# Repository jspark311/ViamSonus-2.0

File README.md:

# Viam Sonus 2.0

An audio router board with integrated volume control and buffered output.

### FEATURES:
  * 12 input channels that are arbitrarily routable to any of 8 output channels.
* Onboard digital potentiometers on the input side with non-volatile storage. Pots are logarithmic with zero-cross detection, and are paired in order with their input numbers on the board's silkscreen.
* Onboard op-amps on the output side with 300mA drive capability to provide buffering for direct-drive of line-level signals.
* Onboard buffered voltage divider with exposed output and 300mA drive capability to aid design and implementation of input buffers.
* Resistors added to the input-side of the switch, but after the potentiometers to allow for simple resistance mixing of signals simply by routing two inputs to a given output without risking damage. Some caveats apply (discussed below).
* Input-side is left free-form to allow use with single-ended (unbalanced) or differential (balanced) signals, and/or DC-biased sources.
* Safe for 5v audio signals.
* Isolated analog and digital power planes.
* Silkscreen reflects the envisioned usage (stereo signals), but the driver allows for easy grouping of any number of channels.
* Breadboard-friendly

#### [Hackaday.io Page](https://hackaday.io/project/168501-viam-sonus-20)

#### [Order from Tindie](https://www.tindie.com/products/18586/)

------------------------

### What is in this repository:

**./doc**:  Location for documentation

**./KiCAD**:  Hardware design files

**./Arduino**:  Arduino driver

**./linux**:  Linux wrappers and utility program

------------------------

### Encountering real world audio signals

#### Mixing, ducking, and cross-fade

To avoid damaging the board, input-side circuits should be designed to limit
peak channel currents if mixing is going to be used. Discourse on that topic can
be found in [a separate document](https://joshianlindsay.com/index.php?id=184).

#### Tips on channel layout

The driver sees the board as 12 mono inputs with discrete volume control routed
to 8 mono outputs. The driver presents a channel-grouping layer to the user application
that largely abstracts the underlying mono channels. But since the DS1881 was
intended as a stereo device, it has properties that support that use...

  * Resistances are matched on its two halves.
  * Both halves can be set with a single bus operation (and thus happen concurrently)

So if you intend on using Viam Sonus to handle stereo inputs, you _can_ use whatever
two channels for left and right that you like, and the driver will make it work. But it
will cost an extra bus operation to set the volume for the pair, and the channel
resistance match might be as loose as +/-20%. So if you can, you will get better
results by keeping stereo pairs on matched channels.

The output channels are also paired into the output buffers, but the choice of
keeping those matched (or not) will have less-tangible consequences.

------------------------

### Notes on driver features:

#### Channel grouping

By default, there are no channel groups, and the API operates on the level of
discrete mono channels. But many application will want to manage _groups of channels_.

Channel groups come in two flavors: Input and Output. Each type has a unique API.

#### Preserve-on-destroy

When the driver instance for the switch is destroyed, the default behavior is to
put the hardware into a known state (reset). This opens all routes. Use-cases
that want the hardware state to outlive the driver's life cycle are possible by
setting preserveOnDestroy(true) ahead of `init()`, like so...

    // Class initializes with the existing state of the hardware.
    vs.preserveOnDestroy(true);
    vs.init(&Wire);

Since `init()` will also call `reset()` by default, preserveOnDestroy must be
enabled prior to `init()` to achieve the desired result (both sides of the driver life cycle).

#### Preserving and restoring hardware states

The driver provides a means of cloning prior states to and from a buffer.
Possible reasons for doing this might be...

  * Higher bus efficiency during `init()`.
  * Major code savings, since you can skip configuring the hardware and the class with discrete function calls.
  * Storage of complete board configurations that can be fully re-established with a minimum of overhead.

Saving the current state can be done like this (from the example sketch)...

    uint8_t buffer[VIAMSONUS_SERIALIZE_SIZE];
    unsigned int written = vs.serialize(buffer, VIAMSONUS_SERIALIZE_SIZE);
    if (VIAMSONUS_SERIALIZE_SIZE == written) {
      // Everything worked. Do what you will with the buffer.
    }

Restoring the state from a buffer can be done either upon construction...

    uint8_t buf[VIAMSONUS_SERIALIZE_SIZE] = {
      0x01, 0x00, 0x00, 0x00, 0x00, 0x01, 0x70, 0x0A, 0x00, 0x00, 0x00, 0x00,
      0x00, 0x00, 0x00, 0x00, 0x00, 0x00, 0x00, 0x00, 0x00, 0x00, 0x01, 0x28,
      0x00, 0x3F, 0x3F, 0x06, 0x01, 0x28, 0x00, 0x3F, 0x3F, 0x06, 0x01, 0x29,
      0x00, 0x3F, 0x3F, 0x06, 0x01, 0x29, 0x00, 0x3F, 0x3F, 0x06, 0x01, 0x2A,
      0x00, 0x3F, 0x3F, 0x06, 0x01, 0x2A, 0x00, 0x3F, 0x3F, 0x06 ...
    };
    ViamSonus vs(buf, VIAMSONUS_SERIALIZE_SIZE);

...or after a successful `init()`...

    // Literally anywhere in the sketch...
    vs.unserialize(buf, VIAMSONUS_SERIALIZE_SIZE);

If done by construction, the configuration will be written to the class immediately,
and to the hardware during `init()`.

Invocation of `unserialize()` will immediately result in I/O as the new
configuration is imparted, but the fields (if any) that are otherwise required for
construction will be ignored.

------------------------

### Usage under Arduino

In order to use this driver, you also need the Arduino drivers for the elements on the board. Clone the following repos into your user libraries (wherever you keep them):

[DS1881 Driver](https://github.com/jspark311/DS1881-Breakout/tree/master/Arduino)

[ADG2128 Driver](https://github.com/jspark311/ADG2128-Breakout/tree/master/Arduino)

[StringBuilder and DataStructures](https://github.com/jspark311/CppPotpourri)

After you've done that, you ought to be able to include the ViamSonus driver.

------------------------

### Usage under Linux

Fortunately, the Viam Sonus router board doesn't have any interrupt pins, which makes running it in userland fairly easy with existing kernel drivers for i2c and GPIO. The reset pin isn't _strictly_ required. It can be tied high.

Just like the Arduino driver, you will need additional libraries. If you've already done
the setup for exposing the GPIO pin and i2c character device in your kernel config, you
ought to be able to do these things...

    git clone https://github.com/jspark311/ViamSonus-2.0.git
    cd ViamSonus-2.0/linux
    ./downloadDeps.sh
    make DEFAULT_I2C_DEV=/dev/i2c-1 DEFAULT_RESET_PIN=/sys/class/gpio/gpio18
    sudo make install

------------------------

Front | Back
:-------:|:------:
  |

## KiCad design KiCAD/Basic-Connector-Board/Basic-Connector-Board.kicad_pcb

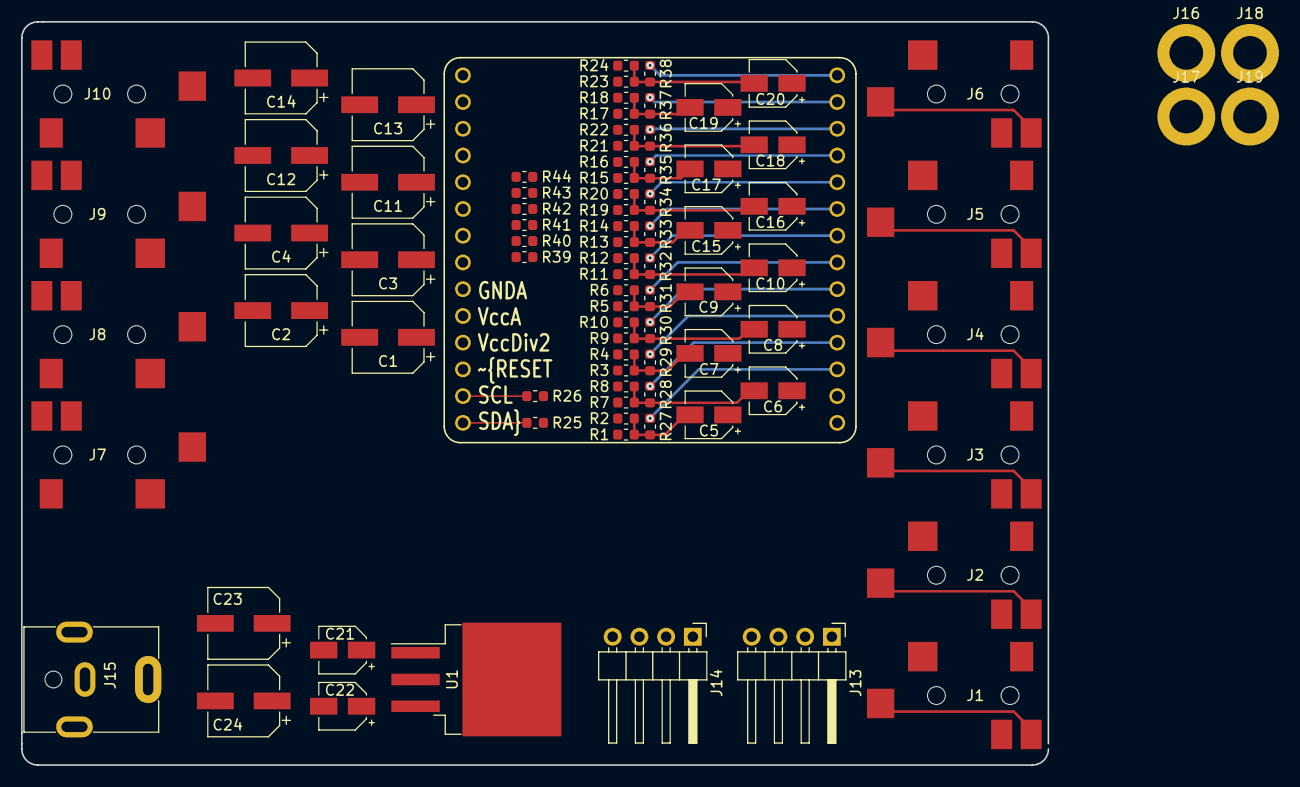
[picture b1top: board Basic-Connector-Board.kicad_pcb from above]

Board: 4 copper layers, 97.5 x 70.6 mm, 88 parts (1 on the bottom side), 67 nets.

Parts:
C1, C2, C3, C4, C11, C12, C13, C14, C23, C24: 100uF; CP_Elec_6.3x5.4_Nichicon
C5, C6, C7, C8, C9, C10, C15, C16, C17, C18, C19, C20: 3.3uF; CP_Elec_4x5.4
C21, C22: 10uF; CP_Elec_4x5.4
J1, J2, J3, J4, J5, J6, J7, J8, J9, J10: AudioJack3_Ground_Switch; SJ2-3593D-SMT-TR
J11, J12: Conn_01x14_Male; PinHeader_1x14_P2.54mm_Vertical
J13, J14: Conn_01x04; PinHeader_1x04_P2.54mm_Horizontal
J15: 6.5 - 20v; PJ-063AH
J16, J17, J18, J19: Conn_01x01; MountingHole_3.2mm_M3_ISO14580_Pad
R1, R2, R3, R4, R5, R6, R7, R8, R9, R10, R11, R12, R13, R14, R15, R16, R17, R18, R19, R20, R21, R22, R23, R24, R39, R40, R41, R42, R43, R44: 20k; R_0603_1608Metric
R25, R26, R27, R28, R29, R30, R31, R32, R33, R34, R35, R36, R37, R38: 2k; R_0603_1608Metric
U1: LM1085; TO-263-3_TabPin2

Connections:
/ANAGND: C21.2, C22.2, C23.2, C24.2, J1.S, J2.S, J3.S, J4.S, J5.S, J6.S, J7.S, J8.S, J9.S, J10.S, J12.6, J13.1, J15.2, R2.1, R4.1, R6.1, R8.1, R10.1, R12.1, R14.1, R16.1, R18.1, R20.1, R22.1, R24.1, U1.2
/ANAVcc: C22.1, C24.1, J12.5, J13.4, R1.1, R3.1, R5.1, R7.1, R9.1, R11.1, R13.1, R15.1, R17.1, R19.1, R21.1, R23.1, U1.3
/Biased-In-L-0: J11.3, R27.2
/Biased-In-L-1: J11.5, R29.2
/Biased-In-L-2: J11.7, R31.2
/Biased-In-L-3: J11.9, R33.2
/Biased-In-L-4: J11.11, R35.2
/Biased-In-L-5: J11.13, R37.2
/Biased-In-R-0: J11.4, R28.2
/Biased-In-R-1: J11.6, R30.2
/Biased-In-R-2: J11.8, R32.2
/Biased-In-R-3: J11.10, R34.2
/Biased-In-R-4: J11.12, R36.2
/Biased-In-R-5: J11.14, R38.2
/GND: J11.2, J13.2, J16.1, J17.1, J18.1, J19.1
/Out-L-0: C1.1, J12.7
/Out-L-1: C3.1, J12.9
/Out-L-2: C11.1, J12.11
/Out-L-3: C13.1, J12.13
/Out-R-0: C2.1, J12.8
/Out-R-1: C4.1, J12.10
/Out-R-2: C12.1, J12.12
/Out-R-3: C14.1, J12.14
/SCL: J12.2, J14.2, R26.2
/SDA: J12.1, J14.3, R25.2
/VIn+: C21.1, C23.1, J15.1, U1.1
/Vcc: J11.1, J13.3, R25.1, R26.1
/VccDiv2: J12.4, J14.4, R39.2, R40.2, R41.2, R42.2, R43.2, R44.2
/~RESET: J12.3, J14.1
unnamed: C1.2, J7.T
unnamed: C2.2, J7.R
unnamed: C3.2, J8.T
unnamed: C4.2, J8.R
unnamed: C5.1, J1.T
unnamed: C5.2, R1.2, R2.2, R27.1
unnamed: C6.1, J1.R
unnamed: C6.2, R7.2, R8.2, R28.1
unnamed: C7.1, J2.T
unnamed: C7.2, R3.2, R4.2, R29.1
unnamed: C8.1, J2.R
unnamed: C8.2, R9.2, R10.2, R30.1
unnamed: C9.1, J3.T
unnamed: C9.2, R5.2, R6.2, R31.1
unnamed: C10.1, J3.R
unnamed: C10.2, R11.2, R12.2, R32.1
unnamed: C11.2, J9.T
unnamed: C12.2, J9.R
unnamed: C13.2, J10.T
unnamed: C14.2, J10.R
unnamed: C15.1, J4.T
unnamed: C15.2, R13.2, R14.2, R33.1
unnamed: C16.1, J4.R
unnamed: C16.2, R19.2, R20.2, R34.1
unnamed: C17.1, J5.T
unnamed: C17.2, R15.2, R16.2, R35.1
unnamed: C18.1, J5.R
unnamed: C18.2, R21.2, R22.2, R36.1
unnamed: C19.1, J6.T
unnamed: C19.2, R17.2, R18.2, R37.1
unnamed: C20.1, J6.R
unnamed: C20.2, R23.2, R24.2, R38.1
unnamed: J1.RN, J1.TN, R39.1
unnamed: J2.RN, J2.TN, R40.1
unnamed: J3.RN, J3.TN, R41.1
unnamed: J4.RN, J4.TN, R42.1
unnamed: J5.RN, J5.TN, R43.1
unnamed: J6.RN, J6.TN, R44.1

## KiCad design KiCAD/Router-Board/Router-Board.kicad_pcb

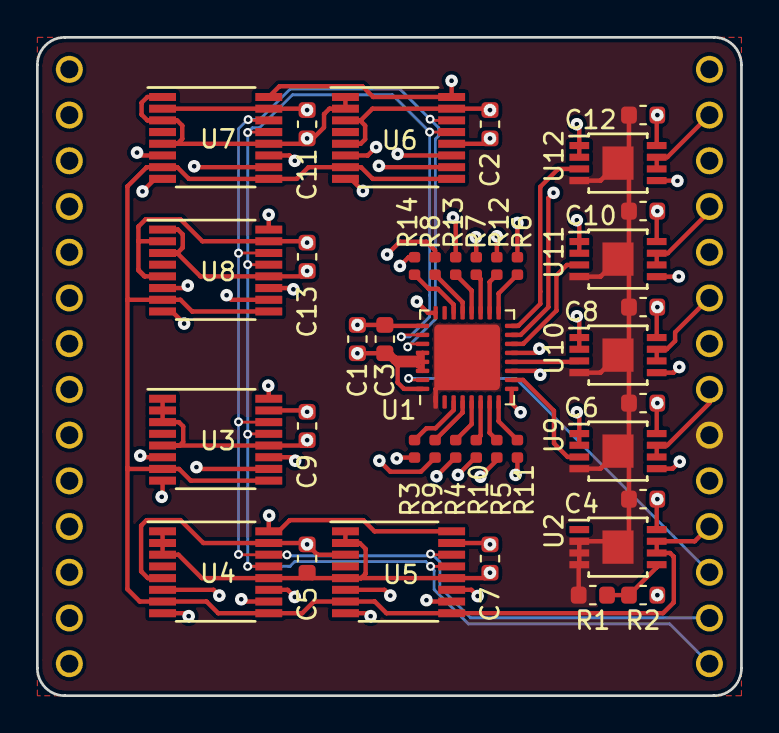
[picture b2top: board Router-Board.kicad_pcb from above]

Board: 4 copper layers, 39.1 x 36.6 mm, 41 parts (1 on the bottom side), 61 nets.

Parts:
C1, C2, C3, C4, C5, C6, C7, C8, C9, C10, C11, C12, C13: 1uF; C_0603_1608Metric
J2, J3: Conn_01x14_Male; PinHeader_1x14_P2.54mm_Vertical
R1, R2: 51k; R_0603_1608Metric
R3, R4, R5, R6, R7, R8, R9, R10, R11, R12, R13, R14: 330; R_0402_1005Metric
U1: ADG2128; QFN-32-1EP_5x5mm_P0.5mm_EP3.65x3.65mm
U2, U9, U10, U11, U12: LME49726MY/NOPB; TSSOP-8_3x3mm_P0.65mm-EP
U3, U4, U5, U6, U7, U8: DS1881E-050+; TSSOP-16_4.4x5mm_P0.65mm

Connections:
/ANAGND: C4.2, C6.2, C8.2, C10.2, C12.2, J3.6, R1.1, U1.1, U1.33, U2.0, U2.2, U2.3, U2.4, U9.0, U9.4, U10.0, U10.4, U11.0, U11.4, U12.0, U12.4
/ANAVcc: C4.1, C6.1, C8.1, C10.1, C12.1, J3.5, R2.2, U1.24, U2.8, U3.16, U4.16, U5.16, U6.16, U7.16, U8.16, U9.8, U10.8, U11.8, U12.8
/Biased-In-L-0: J2.3, U3.8
/Biased-In-L-1: J2.5, U4.8
/Biased-In-L-2: J2.7, U5.8
/Biased-In-L-3: J2.9, U6.8
/Biased-In-L-4: J2.11, U7.8
/Biased-In-L-5: J2.13, U8.8
/Biased-In-R-0: J2.4, U3.10
/Biased-In-R-1: J2.6, U4.10
/Biased-In-R-2: J2.8, U5.10
/Biased-In-R-3: J2.10, U6.10
/Biased-In-R-4: J2.12, U7.10
/Biased-In-R-5: J2.14, U8.10
/GND: C1.2, C2.2, C3.2, C5.2, C7.2, C9.2, C11.2, C13.2, J2.2, U1.28, U1.29, U1.30, U1.32, U3.1, U3.2, U3.3, U3.5, U3.12, U4.1, U4.2, U4.3, U4.12, U5.1, U5.2, U5.5, U5.12, U6.1, U6.2, U6.12, U7.1, U7.3, U7.5, U7.12, U8.1, U8.3, U8.12
/Out-L-0: J3.7, U9.6, U9.7
/Out-L-1: J3.9, U10.6, U10.7
/Out-L-2: J3.11, U11.6, U11.7
/Out-L-3: J3.13, U12.6, U12.7
/Out-R-0: J3.8, U9.1, U9.2
/Out-R-1: J3.10, U10.1, U10.2
/Out-R-2: J3.12, U11.1, U11.2
/Out-R-3: J3.14, U12.1, U12.2
/SCL: J3.2, U1.27, U3.14, U4.14, U5.14, U6.14, U7.14, U8.14
/SDA: J3.1, U1.26, U3.13, U4.13, U5.13, U6.13, U7.13, U8.13
/Switch-In-L-0: R3.1, U3.6
/Switch-In-L-1: R4.1, U4.6
/Switch-In-L-2: R5.1, U5.6
/Switch-In-L-3: R6.1, U6.6
/Switch-In-L-4: R7.1, U7.6
/Switch-In-L-5: R8.1, U8.6
/Switch-In-R-0: R9.1, U3.11
/Switch-In-R-1: R10.1, U4.11
/Switch-In-R-2: R11.1, U5.11
/Switch-In-R-3: R12.1, U6.11
/Switch-In-R-4: R13.1, U7.11
/Switch-In-R-5: R14.1, U8.11
/Switch-Out-L-0: U1.9, U9.5
/Switch-Out-L-1: U1.11, U10.5
/Switch-Out-L-2: U1.13, U11.5
/Switch-Out-L-3: U1.15, U12.5
/Switch-Out-R-0: U1.10, U9.3
/Switch-Out-R-1: U1.12, U10.3
/Switch-Out-R-2: U1.14, U11.3
/Switch-Out-R-3: U1.16, U12.3
/Vcc: C1.1, C2.1, C3.1, C5.1, C7.1, C9.1, C11.1, C13.1, J2.1, U1.25, U3.15, U4.5, U4.15, U5.3, U5.15, U6.3, U6.5, U6.15, U7.2, U7.15, U8.2, U8.5, U8.15
/VccDiv2: J3.4, U2.6, U2.7, U3.7, U3.9, U4.7, U4.9, U5.7, U5.9, U6.7, U6.9, U7.7, U7.9, U8.7, U8.9
/~RESET: J3.3, U1.31
unnamed: R1.2, R2.1, U2.5
unnamed: R3.2, U1.3
unnamed: R4.2, U1.5
unnamed: R5.2, U1.7
unnamed: R6.2, U1.17
unnamed: R7.2, U1.19
unnamed: R8.2, U1.21
unnamed: R9.2, U1.4
unnamed: R10.2, U1.6
unnamed: R11.2, U1.8
unnamed: R12.2, U1.18
unnamed: R13.2, U1.20
unnamed: R14.2, U1.22

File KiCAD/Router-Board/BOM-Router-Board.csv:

Reference, Value, Footprint, Datasheet, Digikey_Num, Manu_Name, Manu_Num
"U1","ADG2128","Package_DFN_QFN:QFN-32-1EP_5x5mm_P0.5mm_EP3.65x3.65mm","","ADG2128YCPZ-REEL7CT-ND","Analog Devices Inc.","ADG2128YCPZ-REEL7"
"U3","DS1881E-050+","Package_SO:TSSOP-16_4.4x5mm_P0.65mm","","DS1881E-050+-ND","Maxim Integrated","DS1881E-050+"
"U11","LME49726MY/NOPB","Footprints:TSSOP-8_3x3mm_P0.65mm-EP","","LME49726MY/NOPBCT-ND","Texas Instruments","LME49726MY/NOPB"
"C10","1uF","Capacitor_SMD:C_0603_1608Metric","~","445-13228-1-ND","TDK Corporation","CGB3B1X7R1A105K055AC"
"U4","DS1881E-050+","Package_SO:TSSOP-16_4.4x5mm_P0.65mm","","DS1881E-050+-ND","Maxim Integrated","DS1881E-050+"
"U5","DS1881E-050+","Package_SO:TSSOP-16_4.4x5mm_P0.65mm","","DS1881E-050+-ND","Maxim Integrated","DS1881E-050+"
"U6","DS1881E-050+","Package_SO:TSSOP-16_4.4x5mm_P0.65mm","","DS1881E-050+-ND","Maxim Integrated","DS1881E-050+"
"U7","DS1881E-050+","Package_SO:TSSOP-16_4.4x5mm_P0.65mm","","DS1881E-050+-ND","Maxim Integrated","DS1881E-050+"
"U8","DS1881E-050+","Package_SO:TSSOP-16_4.4x5mm_P0.65mm","","DS1881E-050+-ND","Maxim Integrated","DS1881E-050+"
"U10","LME49726MY/NOPB","Footprints:TSSOP-8_3x3mm_P0.65mm-EP","","LME49726MY/NOPBCT-ND","Texas Instruments","LME49726MY/NOPB"
"U9","LME49726MY/NOPB","Footprints:TSSOP-8_3x3mm_P0.65mm-EP","","LME49726MY/NOPBCT-ND","Texas Instruments","LME49726MY/NOPB"
"U12","LME49726MY/NOPB","Footprints:TSSOP-8_3x3mm_P0.65mm-EP","","LME49726MY/NOPBCT-ND","Texas Instruments","LME49726MY/NOPB"
"U2","LME49726MY/NOPB","Footprints:TSSOP-8_3x3mm_P0.65mm-EP","","LME49726MY/NOPBCT-ND","Texas Instruments","LME49726MY/NOPB"
"R1","51k","Resistor_SMD:R_0603_1608Metric","~","RMCF0603FT51K0CT-ND","Stackpole Electronics Inc","Stackpole Electronics Inc"
"R3","330","Resistor_SMD:R_0402_1005Metric","~","2019-RK73H1ETTP3300FCT-ND","KOA Speer Electronics, Inc.","RK73H1ETTP3300F"
"J2","Conn_01x14_Male","Connector_PinHeader_2.54mm:PinHeader_1x14_P2.54mm_Vertical","~"
"J3","Conn_01x14_Male","Connector_PinHeader_2.54mm:PinHeader_1x14_P2.54mm_Vertical","~"
"C8","1uF","Capacitor_SMD:C_0603_1608Metric","~","445-13228-1-ND","TDK Corporation","CGB3B1X7R1A105K055AC"
"C6","1uF","Capacitor_SMD:C_0603_1608Metric","~","445-13228-1-ND","TDK Corporation","CGB3B1X7R1A105K055AC"
"C4","1uF","Capacitor_SMD:C_0603_1608Metric","~","445-13228-1-ND","TDK Corporation","CGB3B1X7R1A105K055AC"
"C12","1uF","Capacitor_SMD:C_0603_1608Metric","~","445-13228-1-ND","TDK Corporation","CGB3B1X7R1A105K055AC"
"C1","1uF","Capacitor_SMD:C_0603_1608Metric","~","445-13228-1-ND","TDK Corporation","CGB3B1X7R1A105K055AC"
"C2","1uF","Capacitor_SMD:C_0603_1608Metric","~","445-13228-1-ND","TDK Corporation","CGB3B1X7R1A105K055AC"
"C3","1uF","Capacitor_SMD:C_0603_1608Metric","~","445-13228-1-ND","TDK Corporation","CGB3B1X7R1A105K055AC"
"C5","1uF","Capacitor_SMD:C_0603_1608Metric","~","445-13228-1-ND","TDK Corporation","CGB3B1X7R1A105K055AC"
"C7","1uF","Capacitor_SMD:C_0603_1608Metric","~","445-13228-1-ND","TDK Corporation","CGB3B1X7R1A105K055AC"
"C9","1uF","Capacitor_SMD:C_0603_1608Metric","~","445-13228-1-ND","TDK Corporation","CGB3B1X7R1A105K055AC"
"C11","1uF","Capacitor_SMD:C_0603_1608Metric","~","445-13228-1-ND","TDK Corporation","CGB3B1X7R1A105K055AC"
"C13","1uF","Capacitor_SMD:C_0603_1608Metric","~","445-13228-1-ND","TDK Corporation","CGB3B1X7R1A105K055AC"
"R2","51k","Resistor_SMD:R_0603_1608Metric","~","RMCF0603FT51K0CT-ND","Stackpole Electronics Inc","Stackpole Electronics Inc"
"R9","330","Resistor_SMD:R_0402_1005Metric","~","2019-RK73H1ETTP3300FCT-ND","KOA Speer Electronics, Inc.","RK73H1ETTP3300F"
"R10","330","Resistor_SMD:R_0402_1005Metric","~","2019-RK73H1ETTP3300FCT-ND","KOA Speer Electronics, Inc.","RK73H1ETTP3300F"
"R11","330","Resistor_SMD:R_0402_1005Metric","~","2019-RK73H1ETTP3300FCT-ND","KOA Speer Electronics, Inc.","RK73H1ETTP3300F"
"R12","330","Resistor_SMD:R_0402_1005Metric","~","2019-RK73H1ETTP3300FCT-ND","KOA Speer Electronics, Inc.","RK73H1ETTP3300F"
"R13","330","Resistor_SMD:R_0402_1005Metric","~","2019-RK73H1ETTP3300FCT-ND","KOA Speer Electronics, Inc.","RK73H1ETTP3300F"
"R14","330","Resistor_SMD:R_0402_1005Metric","~","2019-RK73H1ETTP3300FCT-ND","KOA Speer Electronics, Inc.","RK73H1ETTP3300F"
"R8","330","Resistor_SMD:R_0402_1005Metric","~","2019-RK73H1ETTP3300FCT-ND","KOA Speer Electronics, Inc.","RK73H1ETTP3300F"
"R7","330","Resistor_SMD:R_0402_1005Metric","~","2019-RK73H1ETTP3300FCT-ND","KOA Speer Electronics, Inc.","RK73H1ETTP3300F"
"R6","330","Resistor_SMD:R_0402_1005Metric","~","2019-RK73H1ETTP3300FCT-ND","KOA Speer Electronics, Inc.","RK73H1ETTP3300F"
"R5","330","Resistor_SMD:R_0402_1005Metric","~","2019-RK73H1ETTP3300FCT-ND","KOA Speer Electronics, Inc.","RK73H1ETTP3300F"
"R4","330","Resistor_SMD:R_0402_1005Metric","~","2019-RK73H1ETTP3300FCT-ND","KOA Speer Electronics, Inc.","RK73H1ETTP3300F"

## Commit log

2019-11-16 Adding datasheets and updating README.
2019-11-19 Rudaments of Arduino driver. Schematic. README. Renders.
2019-11-19 More driver bulk import with a few passes of rework.
2019-11-20 Adding library trim.
2019-11-23 Adding hardware files. Updated schematic with in-practice resistor values.
2019-11-24 Correcting filename mistake. Adding schematic for recommended input circuit.
2019-11-24 Arduino driver compiles again. Untested.
2019-11-24 Example improvements. Fixing library rename mistake.
2019-11-25 Routing code cleaned up. Switch is now behaving predictably.
2019-11-26 Fixing things after upheaval in dependencies.
2019-11-26 Changing output cap values for better low-end response.
2019-11-27 Adding linux tool. No i2c abstraction yet.
2019-11-29 Adding regulator to connector board. Input-side circuit is now correct.
2019-11-30 More connector board work.
2019-11-30 Adding 3.3v analog regulator symbol.
2019-11-30 Adding some additional features regarding state saves.
2019-11-30 VS class now serializes.
2019-11-30 Implementing unserialize. Untested.
2019-11-30 Bus is now passed in as parameter it init().
2019-12-04 Documentation. work toward sane channel grouping API.
2019-12-04 Makefile work. Doc.
2019-12-04 Simple makefile fixes.
2019-12-05 Connector board work.
2019-12-05 Adding unserialize() demo. Verified working.
2019-12-07 More hardware work. More work on channel groups.
2019-12-07 Mitosis of channel classes reaches telophase.
2019-12-07 More steps toward channel groups.
2019-12-07 Advancing linux support.
2019-12-08 Linux abstractions compile, but TwoWire does nothing.
2019-12-08 Adding sketch for advanced usage.
2019-12-08 More work on the advanced usage example. Compiles and crashes. Basic works great.
2019-12-15 More work toward channel group API.
2019-12-16 Adding capability for timed channel manipulation.
2019-12-18 Fixes, debug cleanup, more unserialize support.
2019-12-18 Fixing a bug in channel swap.
2020-02-22 Reflecting dependency addition to Library manager. Generalizing away from Teensy3.x.
